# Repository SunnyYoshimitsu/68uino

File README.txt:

# 68uino

I started the project sometime after watching a video by Ander Nielson (link below) and got the idea of making something similar. 

Inspiration: https://www.youtube.com/watch?v=s3t2QMukBRs&t=563s&ab_channel=AndersNielsen

However, since he already did the 6502, I decided to use a different processor to challenge myself. Whilst browsing through Jamesco, I found the 6802, a 6800-based CPU. It was very similar to the 6502 due to being designed by the same engineers and most importantly, it had built-in RAM. Doing more research left me with the HD6303 which was the same as the 6202 except with more built-in peripherals. With this chip, I believe I could make a computer even smaller than that of Mr.Nielson's. 

The datasheet of the processor(6303) however had many flaws, like all the odd pages being shown in the beginning and everything else at the end. So I painstakingly reorganized everything start with. The datasheet is posted along with other files here. 

The peripherals on the HD6303 are crazily packed to make it an MCU if not for its lack of ROM. 
Peripherals:
	Timer
	2 GPIO Ports
	Built-in RAM (128 byte)
	built-in clock circuit
	Non-volatile RAM

As one can see, we can already omit GPIOs, RAMs, UART, and timer chips in this design. This makes for a very compact and easy-to-developed system. 

There are two versions of this particular chip. The non-multiplexed 64 pins and the multiplexed 40 pins chip. I've chosen the 40 pin versions for their size, however, that will require me to use a 74ls373 chip to be able to use the multiplexed circuitry, similar to the i8088. Below are the links to the 64 pins(Jamesco), I got my 40 pins from eBay. 

https://www.jameco.com/z/HD6303YP-HITACHI-IC-6303YP-CMOS-8-Bit-MPU-Micro-Processing-Unit-_2287967.html

Designing the system itself, I've decided to make the system compact enough to fit on an Arduino form-factor perf-shield(link below) and running at 1MHz. This is for prototyping purposes and I might move to printing PCBs after since it's cheap provided we use small sizes and in small quantities. 

https://www.aliexpress.us/item/2251832487864030.html?spm=a2g0o.home.0.0.135076db3SfYPj&mp=1&gatewayAdapt=glo2usa

Just making an MCU in itself is very fun, but I also want to make a "field-programmable" MCU to make it a bit more challenging. This meant making a serial monitor program, a human interface, and having an input. I decided to add an SSD1306 screen similar to how Mr.Nielson did his and to add a keyboard interface. Now, in the modern-day, all keyboards are USB-based which is very hard to achieve using a slow and ancient processor. Hence, I opted for the P/S2 interface with a relatively simple architecture. The hope is that I could use that keyboard and type into a monitor program (think WozMon) and it will display on the SSD1306. Also, YES there's only 128 byte on this machine, the same as the 65uino. If I were to make this machine somewhat fully featured, I have to code very efficiently. 

Enough about the ideas and the CPU, let's talk about the system memory layout. This CPU is an 8bit CPU and like the 6502 can only access up to 64k of memory. 

Memory Layout: 
0000 - 001F: Internal Peripheral Registers
001F - 0080: 	Empty
0080 - 00FF: RAM 
6000 - 7FFF: 	Empty
8000 - FFFF: ROM 

And lastly, here's the chips used in this project:
1x 74LS373
1x Ne555
1x 27c256
1x HD6303
1x 4MHz Crystal

Welp....at least that's the plan, I've yet to put it on a per-board and will update when I finish. Thanks for checking this Git/Post!!!!

If you have any question or ideas please don't hesitate to hit me up! I am an active user in the r/beneater subreddit. 
Profile: https://www.reddit.com/user/YoshimitsuSunny

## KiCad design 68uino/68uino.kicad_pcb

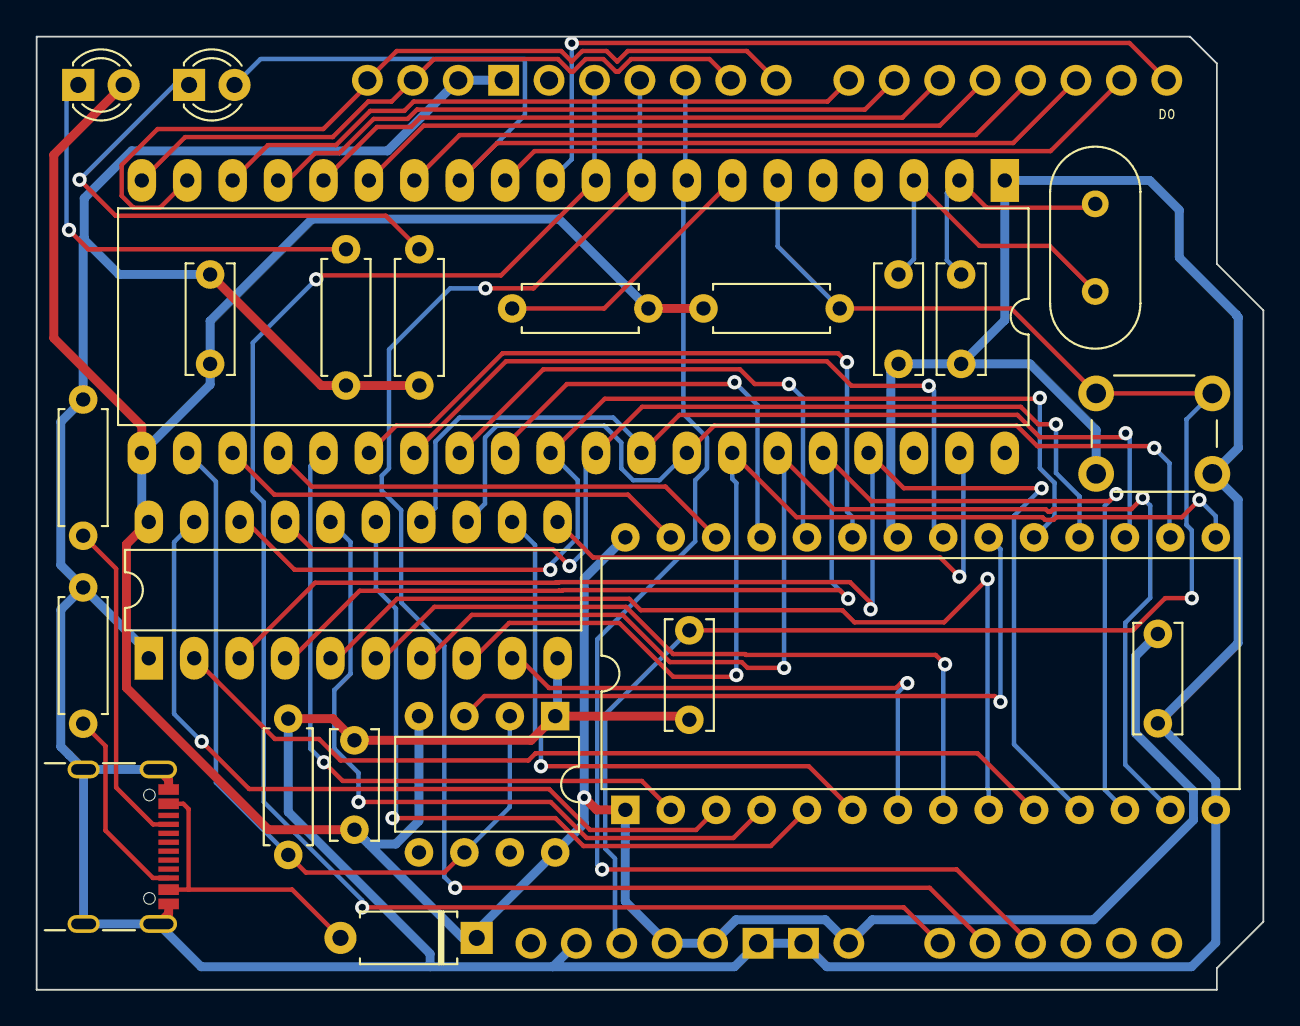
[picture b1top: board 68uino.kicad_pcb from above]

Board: 2 copper layers, 68.6 x 53.3 mm, 24 parts (0 on the bottom side), 50 nets.

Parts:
4MHz1: Crystal; Crystal_HC18-U_Vertical
A1: Arduino_Uno_R3_SMD_Shield; Arduino_6802_Shield
C1, C2: 22pF; C_Disc_D6.0mm_W2.5mm_P5.00mm
C3, C5, C6: .1uF; C_Disc_D6.0mm_W2.5mm_P5.00mm
C4: 10uF; C_Disc_D6.0mm_W2.5mm_P5.00mm
D1: 1N4007; D_A-405_P7.62mm_Horizontal
D2, D3: LED; LED_D3.0mm
R1: 1k; R_Axial_DIN0207_L6.3mm_D2.5mm_P7.62mm_Horizontal
R2, R3, R4, R5, R6, R7: 5k; R_Axial_DIN0207_L6.3mm_D2.5mm_P7.62mm_Horizontal
SW2: SW_Push; SW_PUSH_6mm
U1: HD6303; DIP-40_W15.24mm_LongPads
U2: 27C256; DIP-28_W15.24mm
U4: 74LS373; DIP-20_W7.62mm_LongPads
U5: NE555P; DIP-8_W7.62mm
USB_C_ESP1: USB_C_1; USB_C_Receptacle_GCT_USB4105-xx-A_16P_TopMnt_Horizontal

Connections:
+5V: A1.3V3 (3.3V), A1.5V1 (5V), A1.VIN, C3.1, C5.1, C6.1, D1.1 (K), D2.2 (A), R1.1, R2.1, U1.21 (VCC), U2.1 (VPP), U2.28 (VCC), U4.20 (VCC), U5.4 (R), U5.8 (VCC)
/A8: U1.29 (A8), U2.25 (A8)
/A9: U1.28 (A9), U2.24 (A9)
/A10: U1.27 (A10), U2.21 (A10)
/A11: U1.26 (A11), U2.23 (A11)
/A12: U1.25 (A12), U2.2 (A12)
/A13: U1.24 (A13), U2.26 (A13)
/A14: U1.23 (A14), U2.27 (A14)
/A15: R3.1, U1.22 (A15), U5.2 (TR), U5.6 (THR)
/AD0: U1.37 (AD0), U2.11 (D0), U4.3 (D0)
/AD1: U1.36 (AD1), U2.12 (D1), U4.4 (D1)
/AD2: U1.35 (AD2), U2.13 (D2), U4.7 (D2)
/AD3: U1.34 (AD3), U2.15 (D3), U4.8 (D3)
/AD4: U1.33 (AD4), U2.16 (D4), U4.13 (D4)
/AD5: U1.32 (AD5), U2.17 (D5), U4.14 (D5)
/AD6: U1.31 (AD6), U2.18 (D6), U4.17 (D6)
/AD7: U1.30 (AD7), U2.19 (D7), U4.18 (D7)
AS: U1.39 (AS), U4.11 (LE)
C0: A1.A2, A1.D10 (D10_CS), U1.8 (P20)
C1: A1.A1, A1.D11, U1.9 (P21)
C2: A1.A0, A1.D12, U1.10 (P22)
D0: A1.D2 (D2_INT0), D3.2 (A), U1.13 (P10)
D1: A1.D3 (D3_INT1), U1.14 (P11)
D2: A1.D4, U1.15 (P12)
D3: A1.D5, U1.16 (P13)
D4: A1.D6, U1.17 (P14)
D5: A1.D7, U1.18 (P15)
D6: A1.D8, A1.SCL, U1.19 (P16)
D7: A1.D9, A1.SDA, U1.20 (P17)
GND: A1.AREF, A1.GND1 (GND), A1.GND2 (GND), A1.GND3 (GND), A1.IORF (IOREF), C1.1, C2.1, C3.2, C4.1, C5.2, C6.2, R3.2, R4.1, R5.2, R6.2, R7.1, SW2.1, U1.1 (VSS), U2.14 (GND), U2.22 (~OE), U4.1 (OE), U4.10 (GND), U5.1 (GND), USB_C_ESP1.A1 (GND), USB_C_ESP1.A12 (GND), USB_C_ESP1.B1 (GND), USB_C_ESP1.B12 (GND), USB_C_ESP1.S1 (SHIELD)
unnamed: D1.2 (A), USB_C_ESP1.A4 (VBUS), USB_C_ESP1.A9 (VBUS), USB_C_ESP1.B4 (VBUS), USB_C_ESP1.B9 (VBUS)
unnamed: D2.1 (K), R4.2
unnamed: D3.1 (K), R7.2
unnamed: 4MHz1.1, C2.2, U1.3 (EXTAL)
unnamed: 4MHz1.2, C1.2, U1.2 (XTAL)
unnamed: R1.2, U1.7 (~STBY)
unnamed: U2.10 (A0), U4.2 (O0)
unnamed: U2.9 (A1), U4.5 (O1)
unnamed: U2.8 (A2), U4.6 (O2)
unnamed: U2.7 (A3), U4.9 (O3)
unnamed: U2.6 (A4), U4.12 (O4)
unnamed: U2.5 (A5), U4.15 (O5)
unnamed: U2.4 (A6), U4.16 (O6)
unnamed: U2.3 (A7), U4.19 (O7)
unnamed: R5.1, USB_C_ESP1.A5 (CC1)
unnamed: R6.1, USB_C_ESP1.B5 (CC2)
Reset: A1.RST1 (RESET), C4.2, R2.2, SW2.2, U1.6 (~RES)
Rx: A1.D0 (D0/RX), U1.11 (P23)
Tx: A1.D1 (D1/TX), U1.12 (P24)
~ROM: U2.20 (~CE), U5.3 (Q)

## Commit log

2024-02-21 first commit
    adding all files
2024-09-30 add datashet
    will change the architecture
